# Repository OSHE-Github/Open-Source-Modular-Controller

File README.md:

# Open Source Modular Controller

Using a modular, reconfigurable hardware architecture to create a customizable USB HID game controller.

## Project Details

The Open Source Modular Controller project is a fully modular and customizable gaming input system. Users can freely rearrange joysticks, buttons, and future input modules on a set of interchangeable receiver boards to build a layout that fits their gameplay style, ergonomic needs, or accessibility requirements.

The controller connects over USB and is recognized as a standard Human Interface Device (HID) with no additional drivers required.

## Current State

The current prototype includes:
- A functional ESP32‑S3‑based main controller
- Hot-swappable joystick and button modules
- Receiver boards that can be placed anywhere in the 3D‑printed shell
- USB HID communication via TinyUSB

The system operates as a recognized USB gamepad on Windows. Some hardware issues were identified and corrected in updated revisions.

## Project Structure

The repository is organized as follows:
1. **Firmware** – ESP32‑S3 code handling HID communication and module input processing.  
   *Link: [Firmware](/Controller%20Code/Firmware.md)*
2. **Software** – PC‑side utilities or test scripts (coming soon).  
3. **Hardware** – KiCad project files, schematics, PCBs, and 3D‑printed shell models.  
   *Link: [Hardware](/Hardware/Hardware.md)*
4. **Documentation** – Assembly instructions, diagrams, semester report, and testing notes.  
   *Link: [Documentation](/Documents/Documents.md)*

## Features

- Modular input modules (buttons, joystick, future sensors)
- Repositionable input layout using multiple receiver boards
- ESP32‑S3 native USB HID support
- Open‑source hardware and firmware
- 3D‑printable ergonomic controller shell

## System Architecture

Core system components include:
- **Receiver boards** distributing power, signals, and micro-controller
- **Module boards** for inputs (joystick/button)
- **3D‑printed enclosure** with heat‑set inserts for secure mounting

USB HID enumeration and report handling are implemented using TinyUSB. Modules communicate through standardized connectors to the controller board.

## Bill of Materials
A full BOM including the ESP32‑S3 boards, connector sets, resistors, capacitors, PCBs, wire, and 3D‑printed components is provided in the documentation.  
*[BOM](/Documents/BOM.md)*

## Tools Used
### Software
- Arduino IDE
- KiCad
- OnShape (frame design)
- GitHub Desktop
- Cura slicer

### Hardware
- 3D printer
- Soldering iron
- Hot air station
- Multimeter
- Tweezers

## Assembly Overview
1. Gather materials (refer to BOM).  
2. Order PCBs (Gerber files included).  
3. 3D print shell and module housings.  
4. Clean and prepare boards.  
5. Solder components (headers, ESP32 module, connectors, buttons/joysticks).  
6. Upload firmware via Arduino IDE.  
7. Install modules into the shell.  
8. Test controller.  

[Full assembly guide](/Documents/Assembly%20guide.md)

## What the Project Could Use Next
1. On‑board processing for more advanced input mapping
2. PCB adjustment and testing
3. Wireless mode using Bluetooth HID
4. Additional module types (battery, gyroscope, sliders, touchpads)

## Semester End Report
For the Enterprise Program at Michigan Tech there is a end of semester and project report for the project to summarize the progress of the project. [Link](/Documents/Final%20Report%20Spring%202026.pdf)

## Acknowledgements
This project is supported by the Open Source Hardware Enterprise at Michigan Technological University.

## Helpful Links
- [TinyUSB](https://docs.tinyusb.org/en/latest/)
- [Gamepad tester](https://hardwaretester.com/gamepad)

## References

[GitHub Doc](https://docs.github.com/en/get-started/writing-on-github/getting-started-with-writing-and-formatting-on-github/basic-writing-and-formatting-syntax#links)

[Alpakka conroller](https://inputlabs.io/alpakka)

[Proteus ControllerTM kit](https://byowave.com/products/proteus-controller )

[Thrustmaster](https://eshop.thrustmaster.com/en_us/gamepads/pc.html)

[Adafruit ADS1X15 Library](https://github.com/adafruit/Adafruit_ADS1X15)

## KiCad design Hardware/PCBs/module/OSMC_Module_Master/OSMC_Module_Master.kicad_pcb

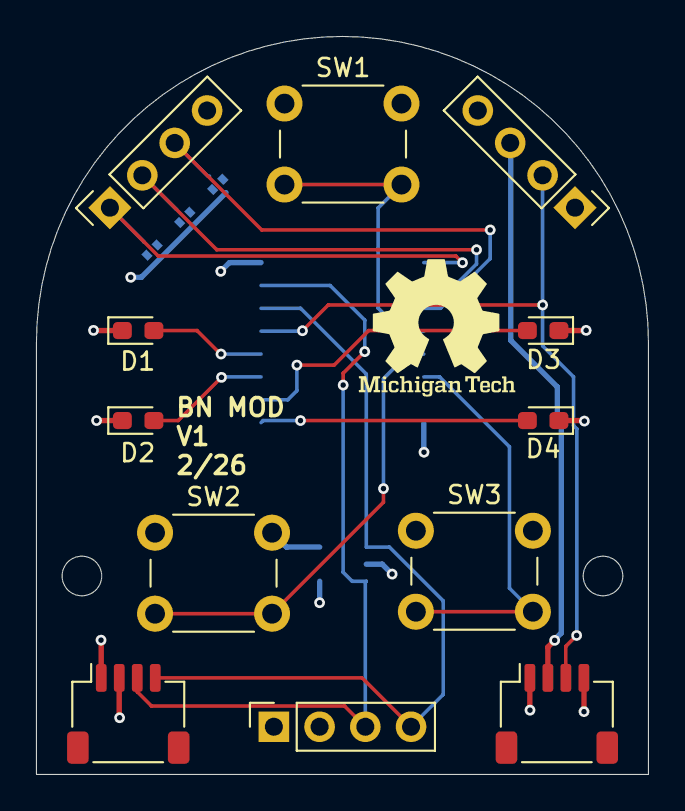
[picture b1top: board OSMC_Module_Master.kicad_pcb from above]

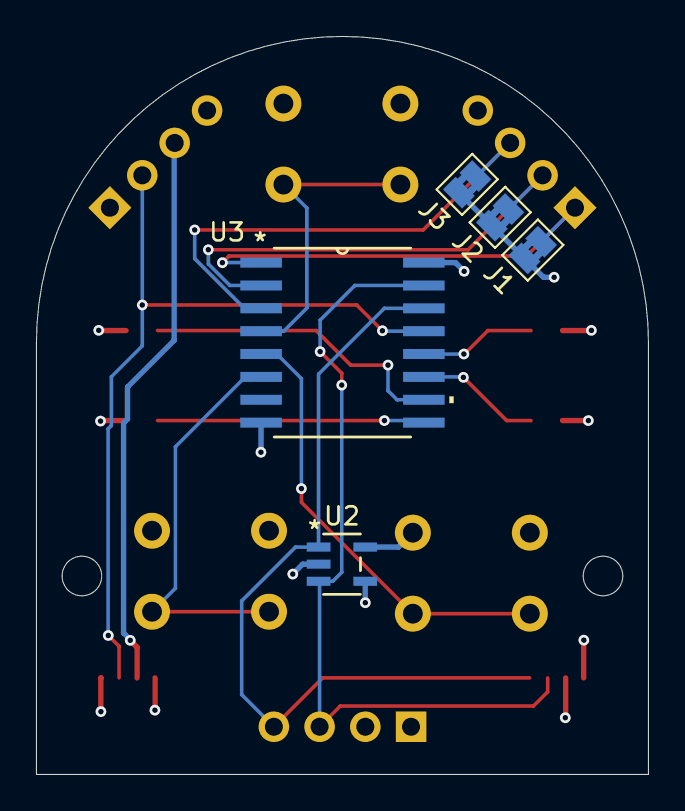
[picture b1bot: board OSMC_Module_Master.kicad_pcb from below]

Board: 4 copper layers, 34.0 x 41.0 mm, 13 parts (5 on the bottom side), 16 nets.

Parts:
D1, D2, D3, D4: LED; LED_0603_1608Metric_Pad1.05x0.95mm_HandSolder
J1, J2, J3: SolderJumper_2_Bridged; SolderJumper-2_P1.3mm_Bridged2Bar_Pad1.0x1.5mm
SW1, SW2, SW3: SW_Push; SW_PUSH_6mm
U1: OSMC Module Board w/pins; Module standard pin large
U2: 24LC02BT-I/OT; SOT-23-5_MC_MCH
U3: PCF8574DWR; DW16

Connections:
/3v3: D1.1 (K), D2.1 (K), D3.1 (K), D4.1 (K), U1.2 (Vdd), U1.6 (Vdd), U1.12 (Det), U1.13 (Int), U2.4 (VCC), U3.16 (VCC)
/5V: U1.10 (5V), U1.15 (5V)
/A0: J1.1 (A), U1.20 (A1), U3.1 (A0)
/A1: J2.1 (A), U1.19 (A2), U3.2 (A1)
/A2: J3.1 (A), U1.18 (A3), U3.3 (A2)
/B1: SW1.2, U3.4 (P0)
/B2: SW2.2, U3.5 (P1)
/B3: SW3.2, U3.6 (P2)
/D1: D1.2 (A), U3.12 (P7)
/D2: D2.2 (A), U3.11 (P6)
/D3: D3.2 (A), U3.10 (P5)
/D4: D4.2 (A), U3.9 (P4)
/INT: U1.11 (OPT), U1.14 (OPT), U3.13 (*INT)
/SCL: U1.4 (SCL), U1.8 (SCL), U2.1 (SCL), U3.14 (SCL)
/SDA: U1.3 (SDA), U1.7 (SDA), U2.3 (SDA), U3.15 (SDA)
GND: J1.2 (B), J2.2 (B), J3.2 (B), SW1.1, SW2.1, SW3.1, U1.1 (Gnd), U1.5 (Gnd), U1.9 (Gnd), U1.16 (GND), U2.2 (VSS), U2.5 (WP), U3.8 (GND)

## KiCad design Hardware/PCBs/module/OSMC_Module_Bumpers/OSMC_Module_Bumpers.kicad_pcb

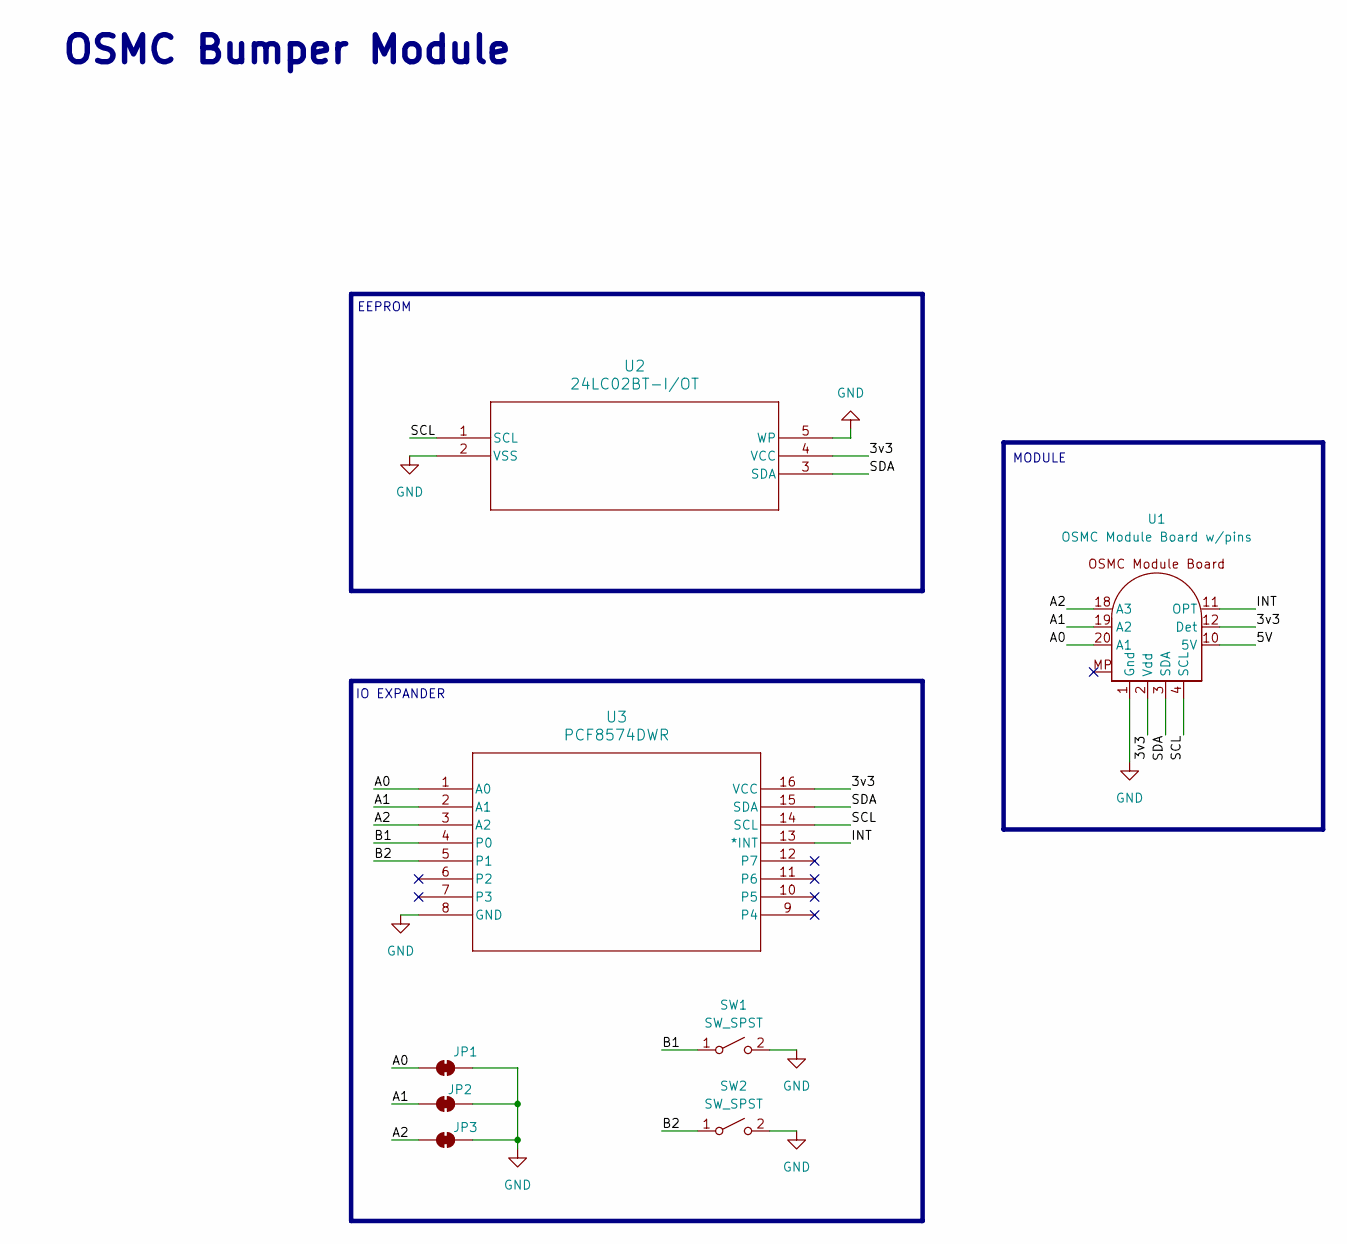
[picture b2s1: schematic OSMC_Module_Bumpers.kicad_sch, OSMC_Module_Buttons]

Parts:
JP1, JP2, JP3: SolderJumper_2_Bridged; SolderJumper-2_P1.3mm_Bridged2Bar_Pad1.0x1.5mm
SW1, SW2: SW_SPST; SW_Cherry_MX_1.00u_PCB
U1: OSMC Module Board w/pins; Module standard pin large
U2: 24LC02BT-I/OT; SOT-23-5_MC_MCH
U3: PCF8574DWR; DW16

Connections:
/3v3: U1.2 (Vdd), U1.6 (Vdd), U1.12 (Det), U1.13 (Int), U2.4 (VCC), U3.16 (VCC)
/5V: U1.10 (5V), U1.15 (5V)
/A0: JP1.1 (A), U1.20 (A1), U3.1 (A0)
/A1: JP2.1 (A), U1.19 (A2), U3.2 (A1)
/A2: JP3.1 (A), U1.18 (A3), U3.3 (A2)
/B1: SW1.1 (A), U3.4 (P0)
/B2: SW2.1 (A), U3.5 (P1)
/INT: U1.11 (OPT), U1.14 (OPT), U3.13 (*INT)
/SCL: U1.4 (SCL), U1.8 (SCL), U2.1 (SCL), U3.14 (SCL)
/SDA: U1.3 (SDA), U1.7 (SDA), U2.3 (SDA), U3.15 (SDA)
GND: JP1.2 (B), JP2.2 (B), JP3.2 (B), SW1.2 (B), SW2.2 (B), U1.1 (Gnd), U1.5 (Gnd), U1.9 (Gnd), U1.16 (GND), U2.2 (VSS), U2.5 (WP), U3.8 (GND)

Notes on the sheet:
EEPROM
IO EXPANDER
OSMC Bumper Module
MODULE

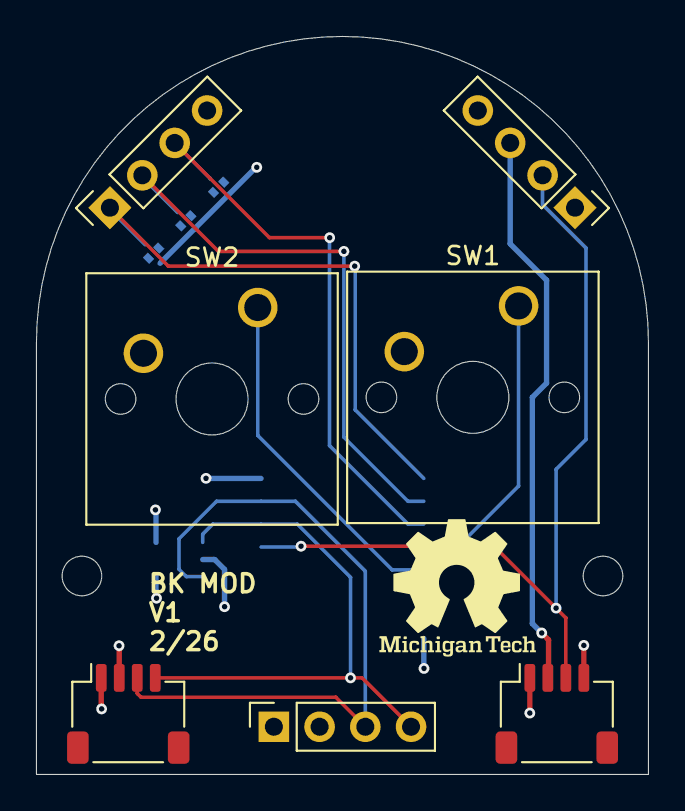
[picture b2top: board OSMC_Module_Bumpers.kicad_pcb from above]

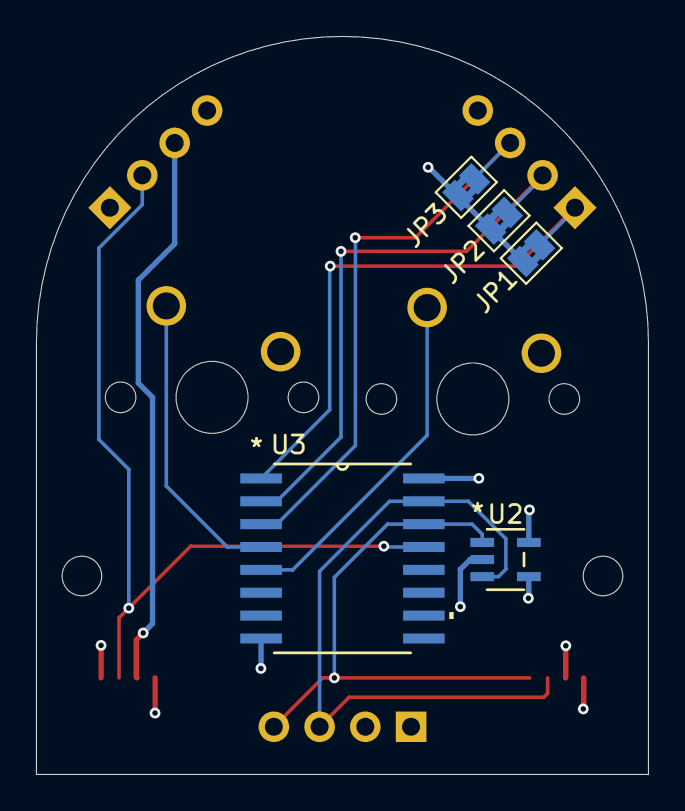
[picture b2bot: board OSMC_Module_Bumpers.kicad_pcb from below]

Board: 4 copper layers, 34.0 x 41.0 mm, 8 parts (5 on the bottom side), 11 nets.

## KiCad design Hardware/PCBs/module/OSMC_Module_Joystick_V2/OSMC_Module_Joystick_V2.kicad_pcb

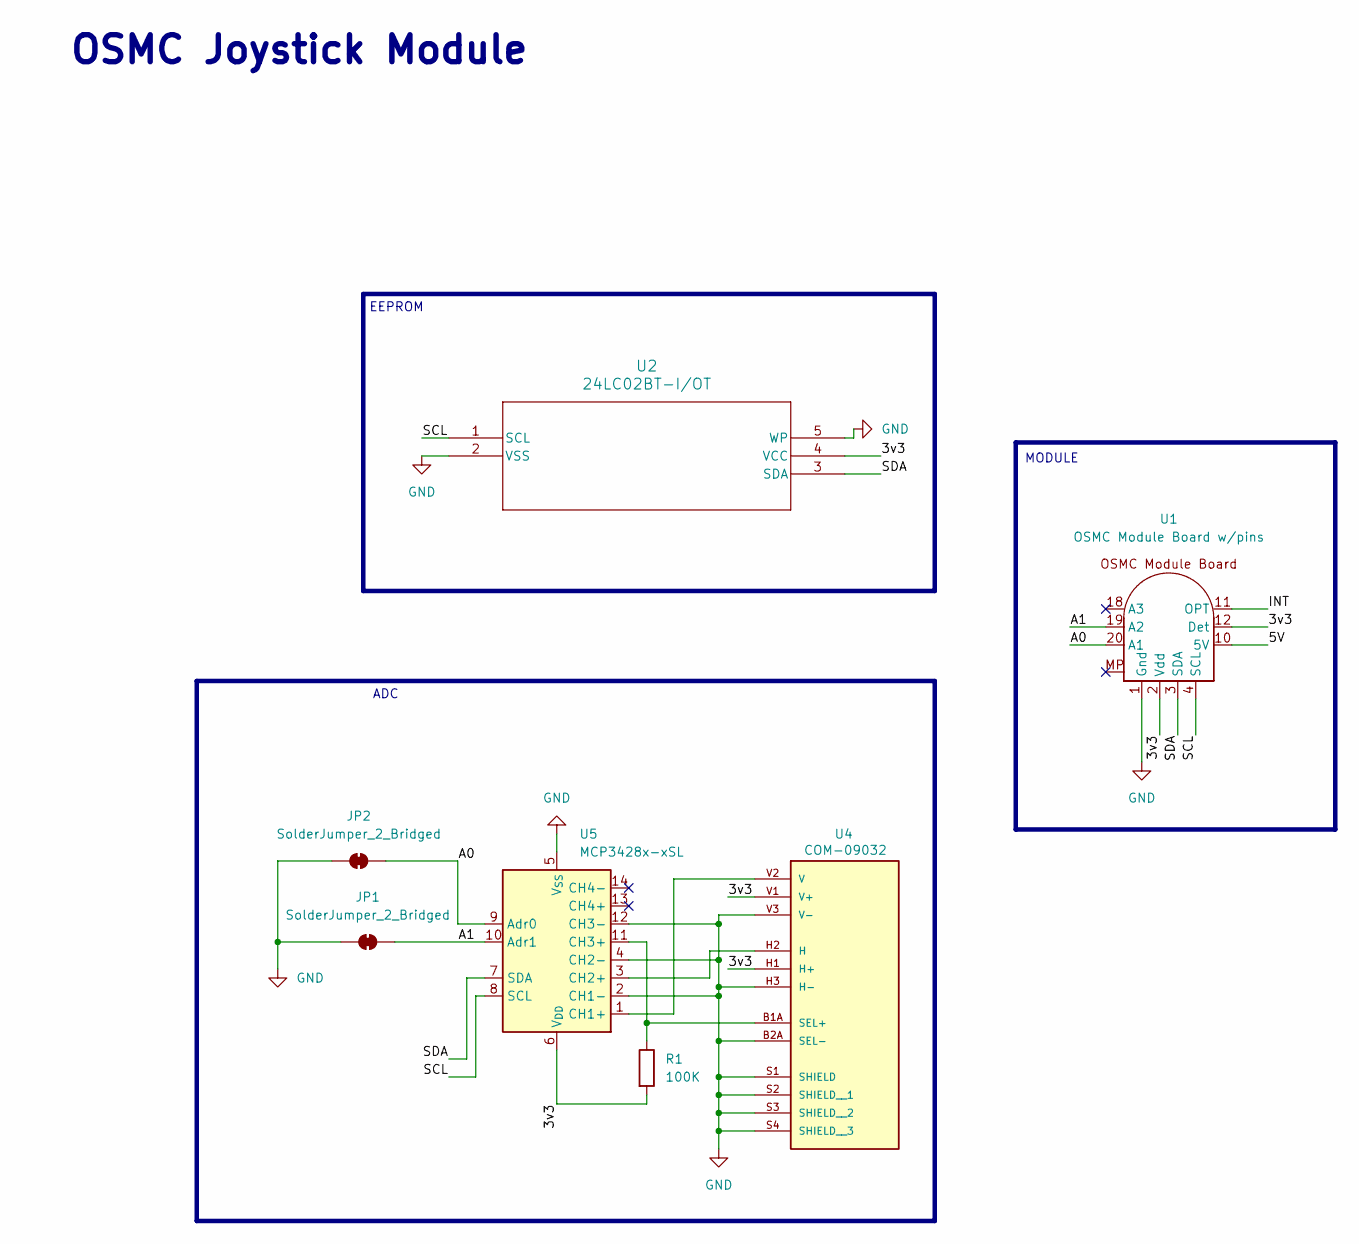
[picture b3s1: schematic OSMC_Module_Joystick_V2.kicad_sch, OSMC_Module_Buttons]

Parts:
JP1, JP2: SolderJumper_2_Bridged; SolderJumper-2_P1.3mm_Bridged2Bar_RoundedPad1.0x1.5mm
R1: 100K; R_0603_1608Metric_Pad0.98x0.95mm_HandSolder
U1: OSMC Module Board w/pins; Module standard pin large
U2: 24LC02BT-I/OT; SOT-23-5_MC_MCH
U4: COM-09032; XDCR_COM-09032; PARTREV N/A
U5: MCP3428x-xSL; SOIC-14_3.9x8.7mm_P1.27mm

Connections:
/3v3: R1.2, U1.2 (Vdd), U1.6 (Vdd), U1.12 (Det), U1.13 (Int), U2.4 (VCC), U4.H1 (H+), U4.V1 (V+), U5.6 (V_{DD})
/5V: U1.10 (5V), U1.15 (5V)
/A0: JP2.2 (B), U1.20 (A1), U5.9 (Adr0)
/A1: JP1.2 (B), U1.19 (A2), U5.10 (Adr1)
/INT: U1.11 (OPT), U1.14 (OPT)
/SCL: U1.4 (SCL), U1.8 (SCL), U2.1 (SCL), U5.8 (SCL)
/SDA: U1.3 (SDA), U1.7 (SDA), U2.3 (SDA), U5.7 (SDA)
GND: JP1.1 (A), JP2.1 (A), U1.1 (Gnd), U1.5 (Gnd), U1.9 (Gnd), U1.16 (GND), U2.2 (VSS), U2.5 (WP), U4.B2A (SEL-), U4.B2B (SEL-), U4.H3 (H-), U4.S1 (SHIELD), U4.S2 (SHIELD__1), U4.S3 (SHIELD__2), U4.S4 (SHIELD__3), U4.V3 (V-), U5.2 (CH1-), U5.4 (CH2-), U5.5 (V_{SS}), U5.12 (CH3-)
unnamed: U4.H2 (H), U5.3 (CH2+)
unnamed: U4.V2 (V), U5.1 (CH1+)
unnamed: R1.1, U4.B1A (SEL+), U4.B1B (SEL+), U5.11 (CH3+)

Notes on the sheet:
EEPROM
ADC
OSMC Joystick Module
MODULE

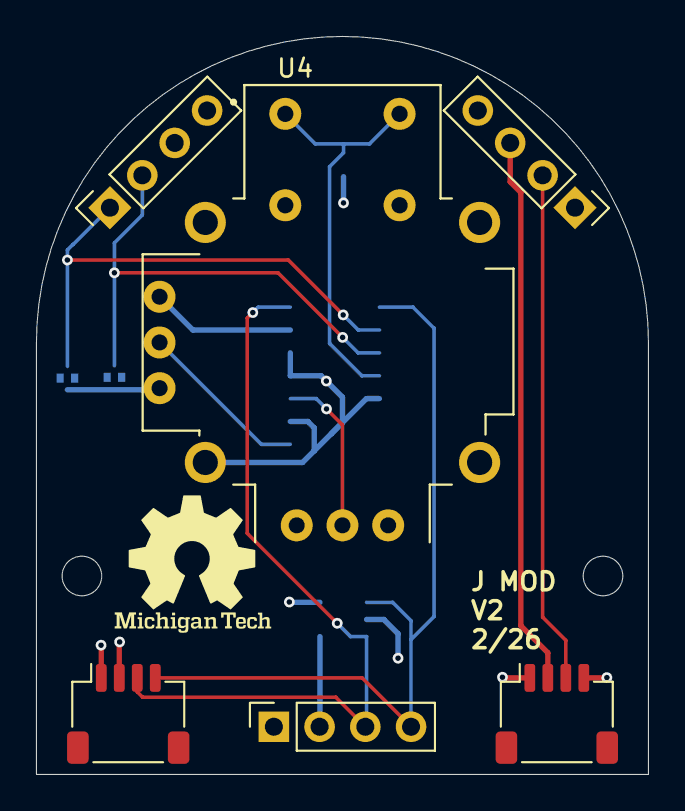
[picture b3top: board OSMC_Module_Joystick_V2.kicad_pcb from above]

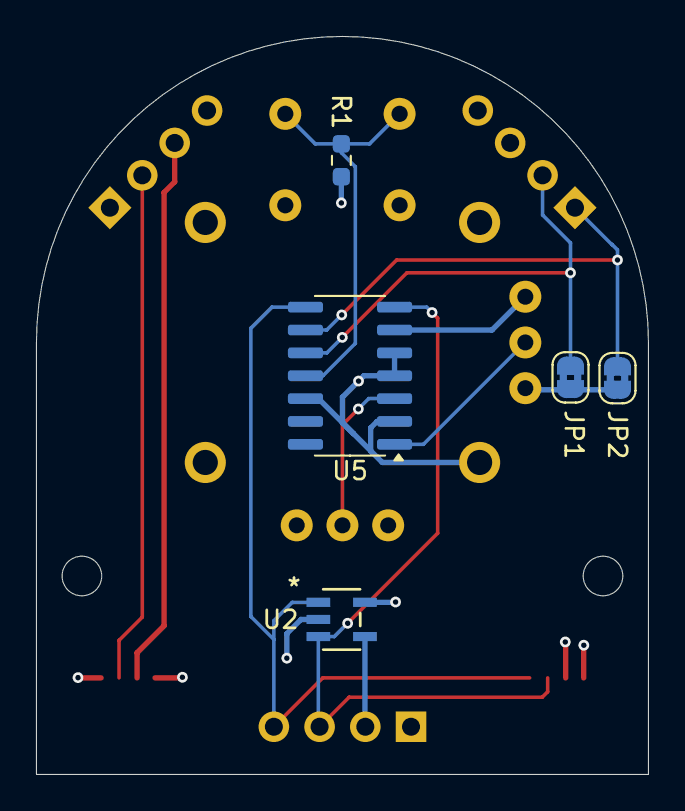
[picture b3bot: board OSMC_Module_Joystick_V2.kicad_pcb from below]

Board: 4 copper layers, 34.0 x 41.0 mm, 7 parts (5 on the bottom side), 11 nets.

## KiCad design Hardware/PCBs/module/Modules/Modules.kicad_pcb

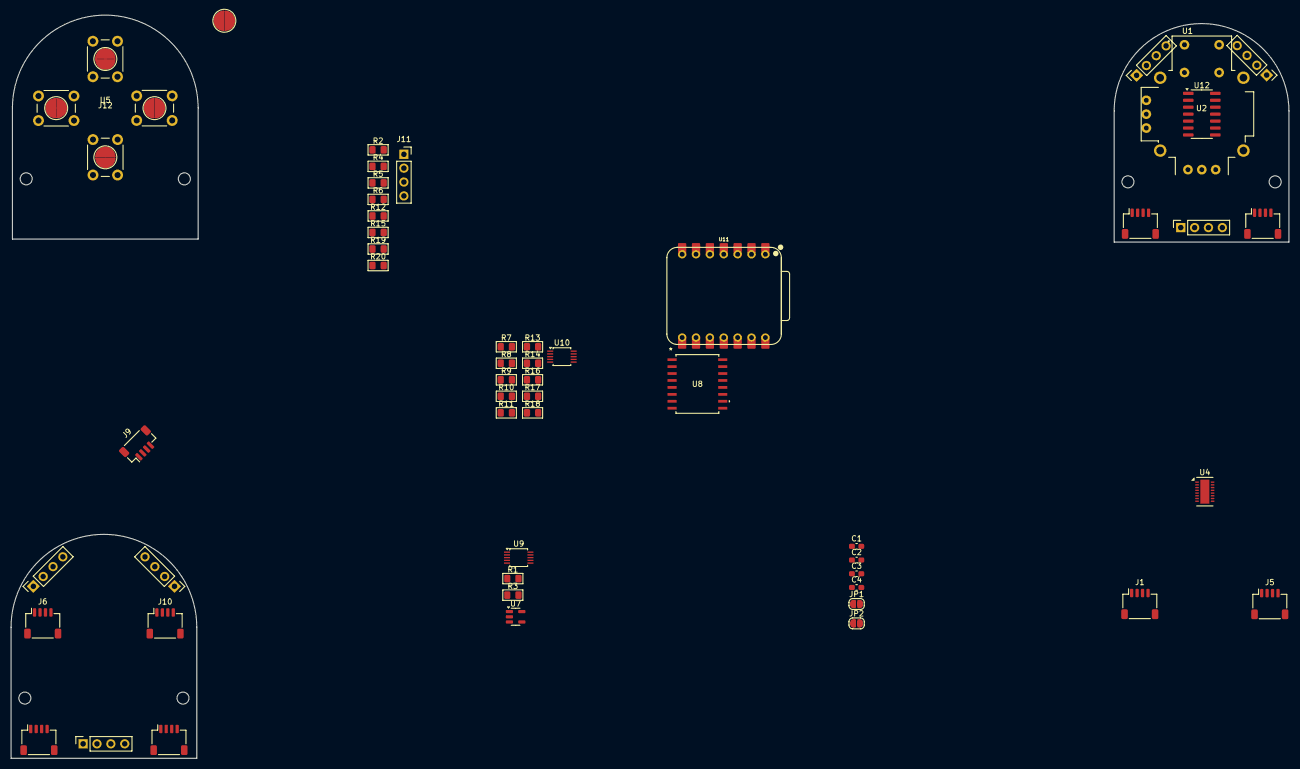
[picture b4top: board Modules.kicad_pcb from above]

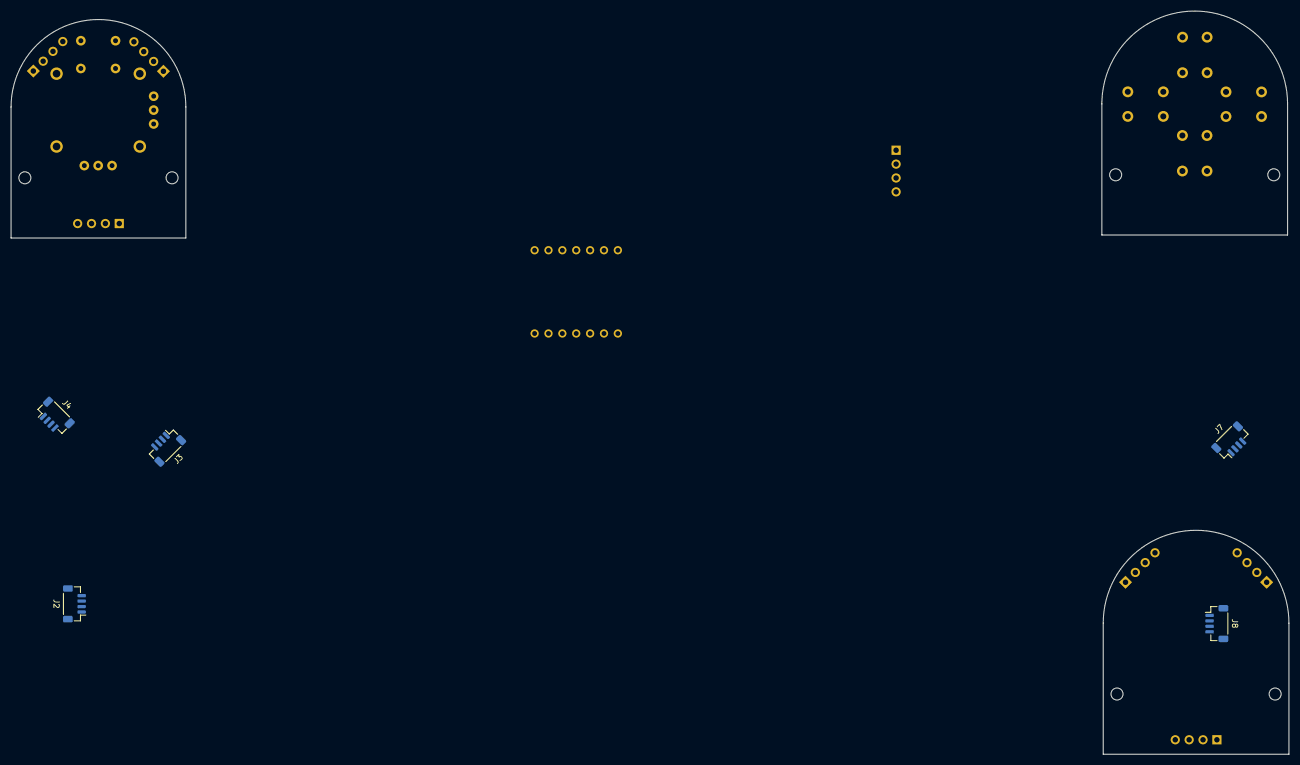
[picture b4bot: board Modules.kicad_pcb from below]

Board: 2 copper layers, 50 parts (5 on the bottom side), 32 nets, no tracks yet.

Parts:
C1, C2: .1 u; C_0603_1608Metric_Pad1.08x0.95mm_HandSolder
C3, C4: C; C_0603_1608Metric_Pad1.08x0.95mm_HandSolder
J1, J5, J6, J10: JST SH; JST_SH_SM04B-SRSS-TB_1x04-1MP_P1.00mm_Horizontal
J2, J3, J4, J7, J8, J9: Conn_01x04; JST_SH_BM04B-SRSS-TB_1x04-1MP_P1.00mm_Vertical
J11: JST SH; PinSocket_1x04_P2.54mm_Vertical
J12: Conn_01x08_Socket; Button Spacing
JP1: WP; SolderJumper-2_P1.3mm_Open_RoundedPad1.0x1.5mm
JP2: Det; SolderJumper-2_P1.3mm_Open_RoundedPad1.0x1.5mm
R1, R2, R3, R4, R5, R6: 100k; R_0805_2012Metric_Pad1.15x1.40mm_HandSolder
R7, R8, R9, R10, R11, R12, R13, R14, R15, R16, R17, R18, R19, R20: 10k; R_0805_2012Metric_Pad1.15x1.40mm_HandSolder
SW1: SW_Push; Membrane Button semi 4 mm
U1: COM-09032; XDCR_COM-09032
U2: OSMC Module Board w/pins; Module standard pin small
U4: OSMC Module Board; DFN-16-1EP_3x5mm_P0.5mm_EP1.66x4.4mm
U5: OSMC Module Board w/pins; Module standard large
U6: OSMC Module Board; Module standard pin large
U7: 24AA02-OT; SOT-23-5
U8: PCF8574DWR; DW16-L
U9: ADS1115IDGS; TSSOP-10_3x3mm_P0.5mm
U10: LTC4317; TSSOP-10_3x3mm_P0.5mm
U11: XIAO-ESP32-S3-DIP
U12: MCP3428x-xSL; SOIC-14_3.9x8.7mm_P1.27mm

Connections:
/5V: C3.1, C4.1, J4.2, J5.2, J9.2, J10.2, U11.14 (5V)
/B0: R2.2, U8.4 (P0)
/B1: R4.2, U8.5 (P1)
/B2: R5.2, U8.6 (P2)
/B3: R6.2, U8.7 (P3)
/Det: J4.4, J9.4, JP2.1 (A), R1.2
/Gnd: C1.2, C2.2, C3.2, C4.2, J1.1, J2.4, J3.2, J3.3, J3.4, J4.1, J5.1, J6.1, J7.2, J7.3, J7.4, J8.4, J9.1, J10.1, J11.1, R1.1, R3.1, U1.B2A (SEL-), U1.H3 (H-), U1.S1 (SHIELD), U1.S2 (SHIELD__1), U1.S3 (SHIELD__2), U1.S4 (SHIELD__3), U1.V3 (V-), U7.2 (V_{SS}), U8.1 (A0), U8.2 (A1), U8.3 (A2), U8.8 (GND), U9.1 (ADDR), U9.3 (GND), U11.13 (GND)
/Opt: J4.3, J9.3
/SCL: J1.4, J2.1, J6.4, J8.1, J11.4, R12.2, U7.1 (SCL), U8.14 (SCL), U9.10 (SCL), U11.6 (PA9_A5_D5_SCL)
/SCL0: R7.2, R8.2
/SCL1: R9.2, R10.2, R20.2, U11.9 (PA7_A8_D8_SCK)
/SDA: J1.3, J2.2, J6.3, J8.2, J11.3, R15.2, U7.3 (SDA), U8.15 (SDA), U9.9 (SDA), U11.5 (PA8_A4_D4_SDA)
/SDA1: R19.2, U11.10 (PA5_A9_D9_MISO)
/Vdd: C1.1, C2.1, J1.2, J2.3, J6.2, J8.3, J11.2, JP1.2 (B), JP2.2 (B), R2.1, R4.1, R5.1, R6.1, R12.1, R15.1, R19.1, R20.1, U1.H1 (H+), U1.V1 (V+), U7.4 (V_{CC}), U8.16 (VDD), U9.8 (VDD), U11.12 (3V3)
/X1: U1.H2 (H), U9.5 (AIN1)
/Y1: U1.V2 (V), U9.4 (AIN0)
/Z1: U1.B1A (SEL+), U9.7 (AIN3)
/int: J5.4, J10.4, U8.13 (~INT), U9.2 (ALERT/RDY)
/wp: JP1.1 (A), R3.2, U7.5 (WP)
GND: R13.2, R16.2, U10.1 (GND), U10.3 (XORH2), U10.4 (XORL2)
unnamed: U2.10 (5V), U2.15 (5V)
unnamed: U2.12 (Det), U2.13 (Det)
unnamed: U2.1 (Gnd), U2.5 (Gnd), U2.9 (Gnd), U2.16 (GND)
unnamed: U2.11 (OPT), U2.14 (OPT)
unnamed: U2.4 (SCL), U2.8 (SCL)
unnamed: U2.3 (SDA), U2.7 (SDA)
unnamed: U2.2 (Vdd), U2.6 (Vdd)
unnamed: R18.2, U10.8 (ENABLE1)
unnamed: R17.2, U10.2 (ENABLE2)
unnamed: R11.2, R13.1, U10.5 (XORH1)
unnamed: R14.2, R16.1, U10.6 (XORL1)
VDD: R7.1, R8.1, R9.1, R10.1, R11.1, R14.1, R17.1, R18.1, U10.7 (VCC)

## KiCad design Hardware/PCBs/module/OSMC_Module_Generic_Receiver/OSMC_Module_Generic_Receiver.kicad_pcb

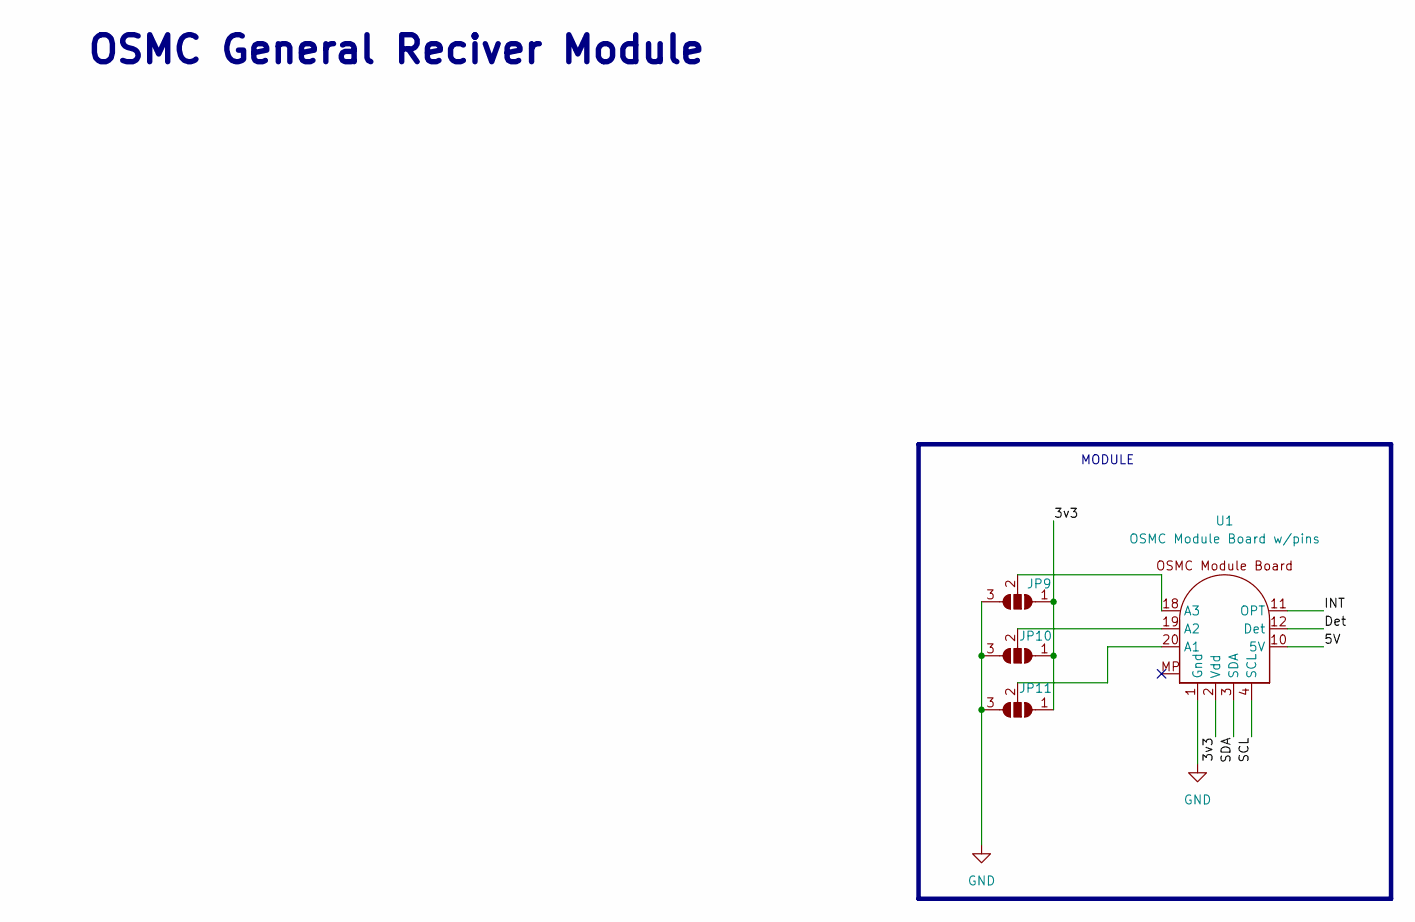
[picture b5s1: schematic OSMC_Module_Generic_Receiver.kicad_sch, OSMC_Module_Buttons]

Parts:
JP9, JP10, JP11: SolderJumper_3_Open; SolderJumper-3_P1.3mm_Open_Pad1.0x1.5mm
U1: OSMC Module Board w/pins; Module standard pin large

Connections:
/3v3: JP9.1 (A), JP10.1 (A), JP11.1 (A), U1.2 (Vdd), U1.6 (Vdd)
/5V: U1.10 (5V), U1.15 (5V)
/Det: U1.12 (Det), U1.13 (Int)
/INT: U1.11 (OPT), U1.14 (OPT)
/SCL: U1.4 (SCL), U1.8 (SCL)
/SDA: U1.3 (SDA), U1.7 (SDA)
GND: JP9.3 (B), JP10.3 (B), JP11.3 (B), U1.1 (Gnd), U1.5 (Gnd), U1.9 (Gnd), U1.16 (GND)
unnamed: JP9.2 (C), U1.18 (A3)
unnamed: JP10.2 (C), U1.19 (A2)
unnamed: JP11.2 (C), U1.20 (A1)

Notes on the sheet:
OSMC General Reciver Module
MODULE

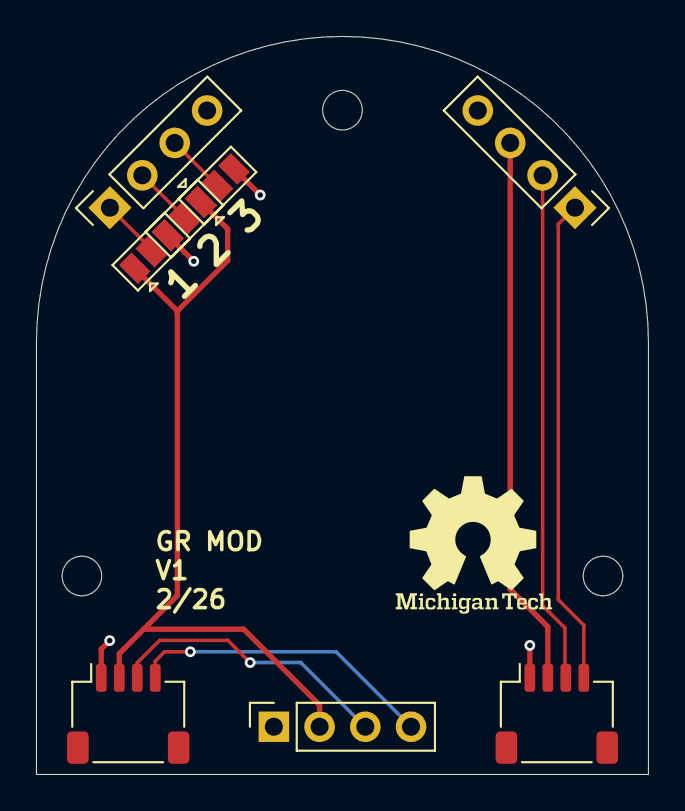
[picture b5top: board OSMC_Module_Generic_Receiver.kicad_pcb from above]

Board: 2 copper layers, 34.0 x 41.0 mm, 4 parts (0 on the bottom side), 10 nets.
